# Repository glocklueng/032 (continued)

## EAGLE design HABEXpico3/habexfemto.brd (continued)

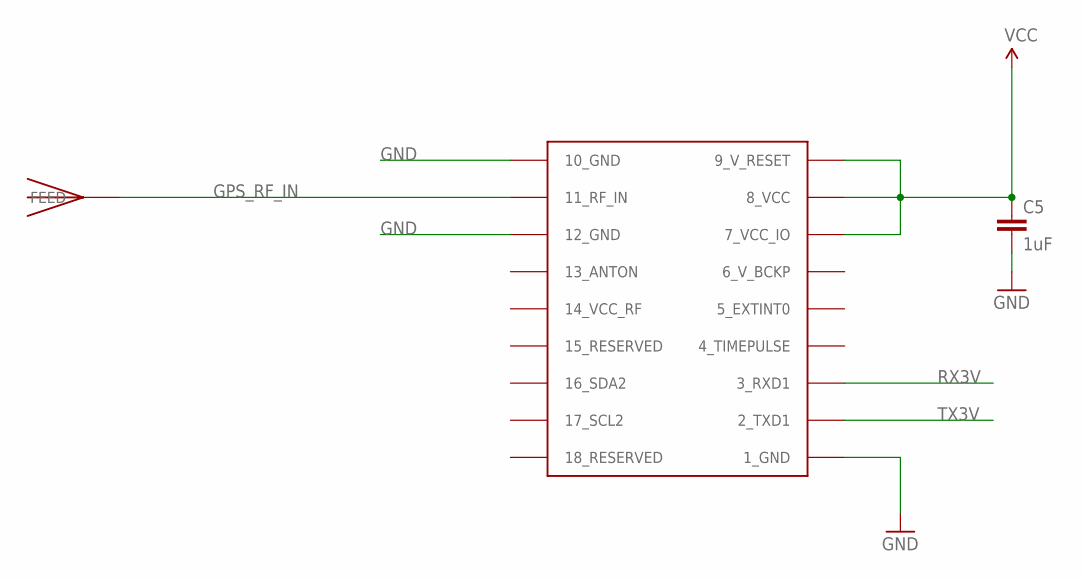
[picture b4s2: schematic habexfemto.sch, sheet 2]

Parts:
C5: 1uF; 0402-CAP
U$2: UBLOX_MAX-6
U$3: JTI_ANTENNA-1575AT43A40

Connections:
GND: C5.2, U$2.1_GND, U$2.10_GND, U$2.12_GND; also elsewhere on the board
GPS_RF_IN: U$2.11_RF_IN, U$3.FEED
RX3V: U$2.3_RXD1; also elsewhere on the board
TX3V: U$2.2_TXD1; also elsewhere on the board
VCC: C5.1, U$2.7_VCC_IO, U$2.8_VCC, U$2.9_V_RESET; also elsewhere on the board

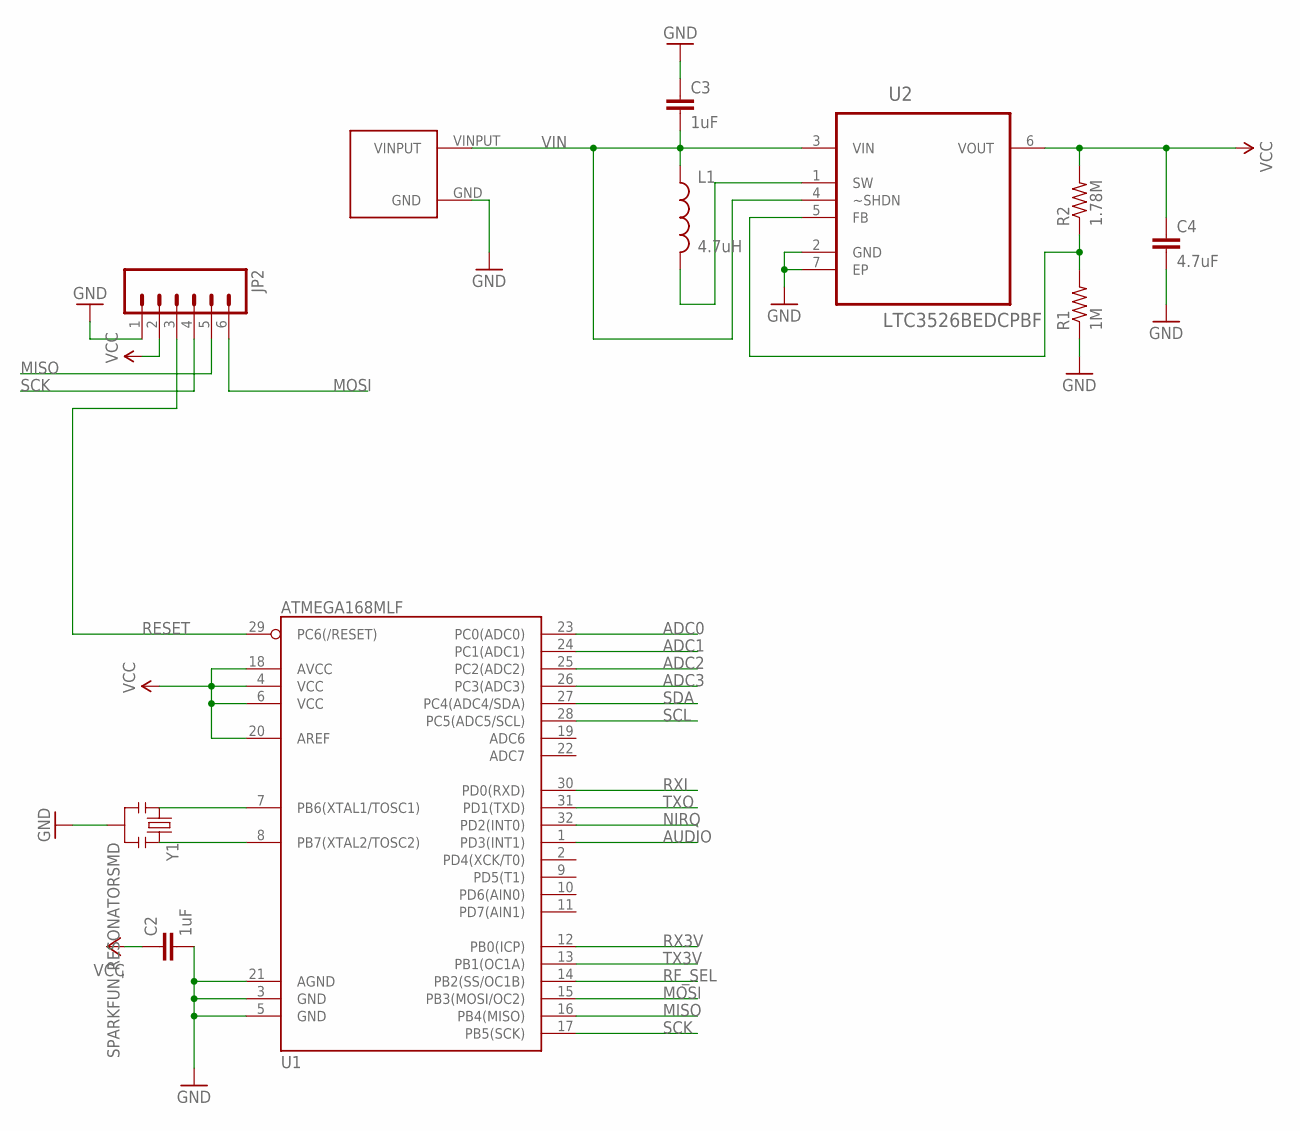
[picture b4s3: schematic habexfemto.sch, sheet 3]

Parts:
C2, C3: 1uF; 0402-CAP
C4: 4.7uF; 0402-CAP
JP2: M06EM406; EM406
L1: 4.7uH; 0603
R1: 1M; 0402-RES
R2: 1.78M; 0402-RES
U1: ATMEGA168MLF; MLF32
U2: LTC3526BEDCPBF; DFN200X200X80-7N
U$5: POWERPADS
Y1: SPARKFUN_RESONATORSMD; SPARKFUN_RESONATOR-SMD

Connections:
ADC0: U1.23 (PC0(ADC0))
ADC1: U1.24 (PC1(ADC1))
ADC2: U1.25 (PC2(ADC2))
ADC3: U1.26 (PC3(ADC3))
AUDIO: U1.1 (PD3(INT1)); also elsewhere on the board
GND: C2.2, C3.1, C4.2, JP2.1, R1.1, U1.3 (GND), U1.5 (GND), U1.21 (AGND), U2.2 (GND), U2.7 (EP), U$5.GND, Y1.2; also elsewhere on the board
MISO: JP2.5, U1.16 (PB4(MISO)); also elsewhere on the board
MOSI: JP2.6, U1.15 (PB3(MOSI/OC2)); also elsewhere on the board
unnamed: U1.7 (PB6(XTAL1/TOSC1)), Y1.1
unnamed: U1.8 (PB7(XTAL2/TOSC2)), Y1.3
unnamed: L1.2, U2.1 (SW)
unnamed: R1.2, R2.1, U2.5 (FB)
NIRQ: U1.32 (PD2(INT0)); also elsewhere on the board
RESET: JP2.3, U1.29 (PC6(/RESET))
RF_SEL: U1.14 (PB2(SS/OC1B)); also elsewhere on the board
RX3V: U1.12 (PB0(ICP)); also elsewhere on the board
RXI: U1.30 (PD0(RXD))
SCK: JP2.4, U1.17 (PB5(SCK)); also elsewhere on the board
SCL: U1.28 (PC5(ADC5/SCL))
SDA: U1.27 (PC4(ADC4/SDA))
TX3V: U1.13 (PB1(OC1A)); also elsewhere on the board
TXO: U1.31 (PD1(TXD))
VCC: C2.1, C4.1, JP2.2, R2.2, U1.4 (VCC), U1.6 (VCC), U1.18 (AVCC), U1.20 (AREF), U2.6 (VOUT); also elsewhere on the board
VIN: C3.2, L1.1, U2.3 (VIN), U2.4 (~SHDN), U$5.VINPUT

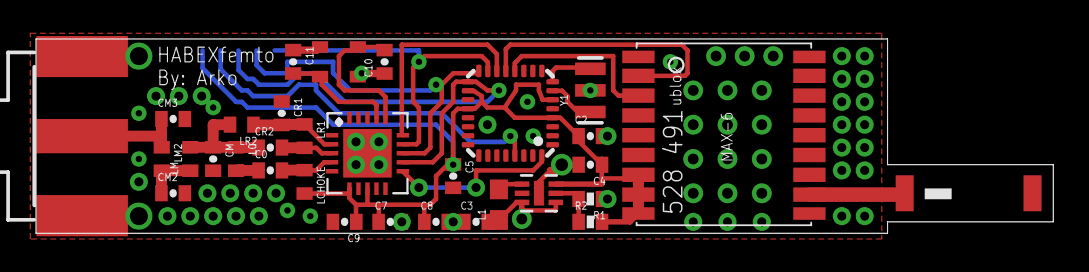
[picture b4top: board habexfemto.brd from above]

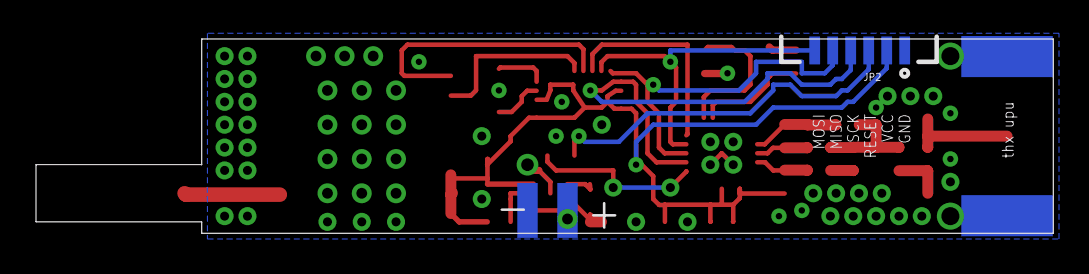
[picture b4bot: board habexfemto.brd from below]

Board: 2 copper layers, 56.5 x 10.8 mm, 34 parts (2 on the bottom side), 26 nets.

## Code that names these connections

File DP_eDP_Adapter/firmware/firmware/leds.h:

#ifndef _RF_BLINKY_H_
#define _RF_BLINKY_H_ ( 1 )

#define F_CPU (8000000)

// includes

#include <avr/io.h>
#include <util/delay.h>
#include <avr/interrupt.h>
#include <avr/sfr_defs.h>

#include <math.h> 
#include <avr/eeprom.h>
#include <avr/sleep.h>
#include <avr/power.h>
#include <avr/pgmspace.h>

#include <stdlib.h>
#include <string.h>
#include <math.h>

// typedefs

typedef unsigned char uchar;
typedef unsigned int uint;

// structures

// defines
#define LEDS_HEIGHT ( 12 )
#define LEDS_WIDTH ( 6 )

#define NUM_TLC5947 (LEDS_HEIGHT * LEDS_WIDTH )

#define bit_set(reg, bit) reg |= 1 << bit 
#define bit_clr(reg, bit) reg &= ~(1 << bit) 

#ifndef TWO_PI
#define TWO_PI                 ( 6.283185307f )
#endif

#define DATPIN		( PB1 )    //    SIN
#define CLKPIN		( PB2 )
#define BLANKPIN	( PB3 ) 
#define LATPIN		( PB4 )

#define SIN_PIN     ( PB1 ) /// PC0
#define SCLK_PIN	( PB2 ) /// PC1
#define BLANK_PIN	( PB3 ) /// PC2
#define XLAT_PIN    ( PB4 ) /// PC3a

extern uint8_t LEDChannels[(NUM_TLC5947)];
extern unsigned char brightnessShift;

// prototypes
void Clear(unsigned char val);

// TLC
void WriteLEDArray(unsigned char count);
void LED_Init(void);
void WriteArrayOffset(unsigned int count, unsigned int offset);

#endif
